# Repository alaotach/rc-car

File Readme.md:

# Quixie - RC Delivery Car

Quixie is a small autonomous RC delivery car. The custom PCB handles motor control and sensor expansion; the firmware manages navigation, telemetry, and the locking cargo bay.

> Built by **AlAoTach** for [Fallout](https://fallout.hackclub.com/)

---

## Why I Built This

I wanted to steal chips from my nephew.

---

## Key Features

- **Servo locked cargo bay** - lid opens and closes automatically via servo motor
- **Live camera feed** - ESP32-CAM streamed to the web dashboard
- **GPS navigation** - Neo-8M for real-time position tracking
- **Obstacle avoidance** - 3× ultrasonic sensors
- **OLED display** - SSD1306 1.3" on-device status screen
---

## Tech Specs

| Component | Part |
|-----------|------|
| MCU | ESP32 Mini (ESP32-S3) |
| Motors | Dual DC Geared, 12V |
| Driver | BTN7960B (43A) |
| GPS | Neo-6M |
| IMU | BMI270 |
| Sensors | Ultrasonic ×3 |
| Camera | ESP32-CAM |
| Display | SSD1306 OLED (1.11") |
| Battery | 3S Li-ion (11.1V) |
| Comms | WiFi — Web + WebSocket |

---

## System Overview

---

## What's in This Repo

```
quixie/
├── pcb/                          # KiCad project
│   ├── rc-car.kicad_pcb          # PCB layout
│   ├── rc-car.kicad_sch          # Schematic
│   ├── rc-car.kicad_pro          # Project file
│   ├── rc-car-BOM.csv            # Bill of materials
│   └── fabrication/              # Gerbers + drill files
├── firmware/
│   └── rc-car/
│       ├── include/              # Header files + Config.h
│       └── src/                  # Source files
├── fabrication/
│   └── 3d/
│       ├── rc-car-case.f3d       # Fusion 360 CAD source
│       ├── rc-car-case.stl       # 3D printable case
│       └── pcb-model.stl         # 3D PCB model
└── docs/assets/                  # Images and media
```

---

## PCB

Front and back of the custom PCB:

---

## 3D Case

The case is 3D printable in PLA.

**Open cargo bay**

---

## Schematic

### Main schema

### Motor schema

### Ultrasonic and TOF

### Servo lock

### Voltage divider

### Battery and charging

---

## Build Guide

### Step 1 - Export Gerbers

Open `pcb/rc-car.kicad_pcb` in KiCad. Generate Gerbers and drill files into `pcb/fabrication/`. Zip all outputs.

### Step 2 - Order the PCB

Upload your Gerber zip to [JLCPCB](https://jlcpcb.com) or your preferred fab.

### Step 3 - Solder & Populate

Solder the required components ( hope you have gotten SMD from jlcpcb )

### Step 4 - Flash Firmware

```bash
cd firmware/rc-car
pio run --target upload
```

Requires [PlatformIO](https://platformio.org/). Main config is in `firmware/rc-car/include/Config.h`.

### Step 5 - 3D Print the Case

- Material: PLA (PETG also works)
- File: `fabrication/3d/rc-car-case.stl`
- No supports needed for most orientations

### Step 6 - Final Assembly

Mount the PCB in the case, wire motors and power, connect sensors. The servo for the lid attaches at the rear hinge point.

---

## Modifying the Firmware

All config parameters live in:

```
firmware/rc-car/include/Config.h
```

Features are split into modules under `firmware/rc-car/src/`.

---

## License

Open source. Do what you want, just don't use it to steal chips from *my* nephew *cough cough*.

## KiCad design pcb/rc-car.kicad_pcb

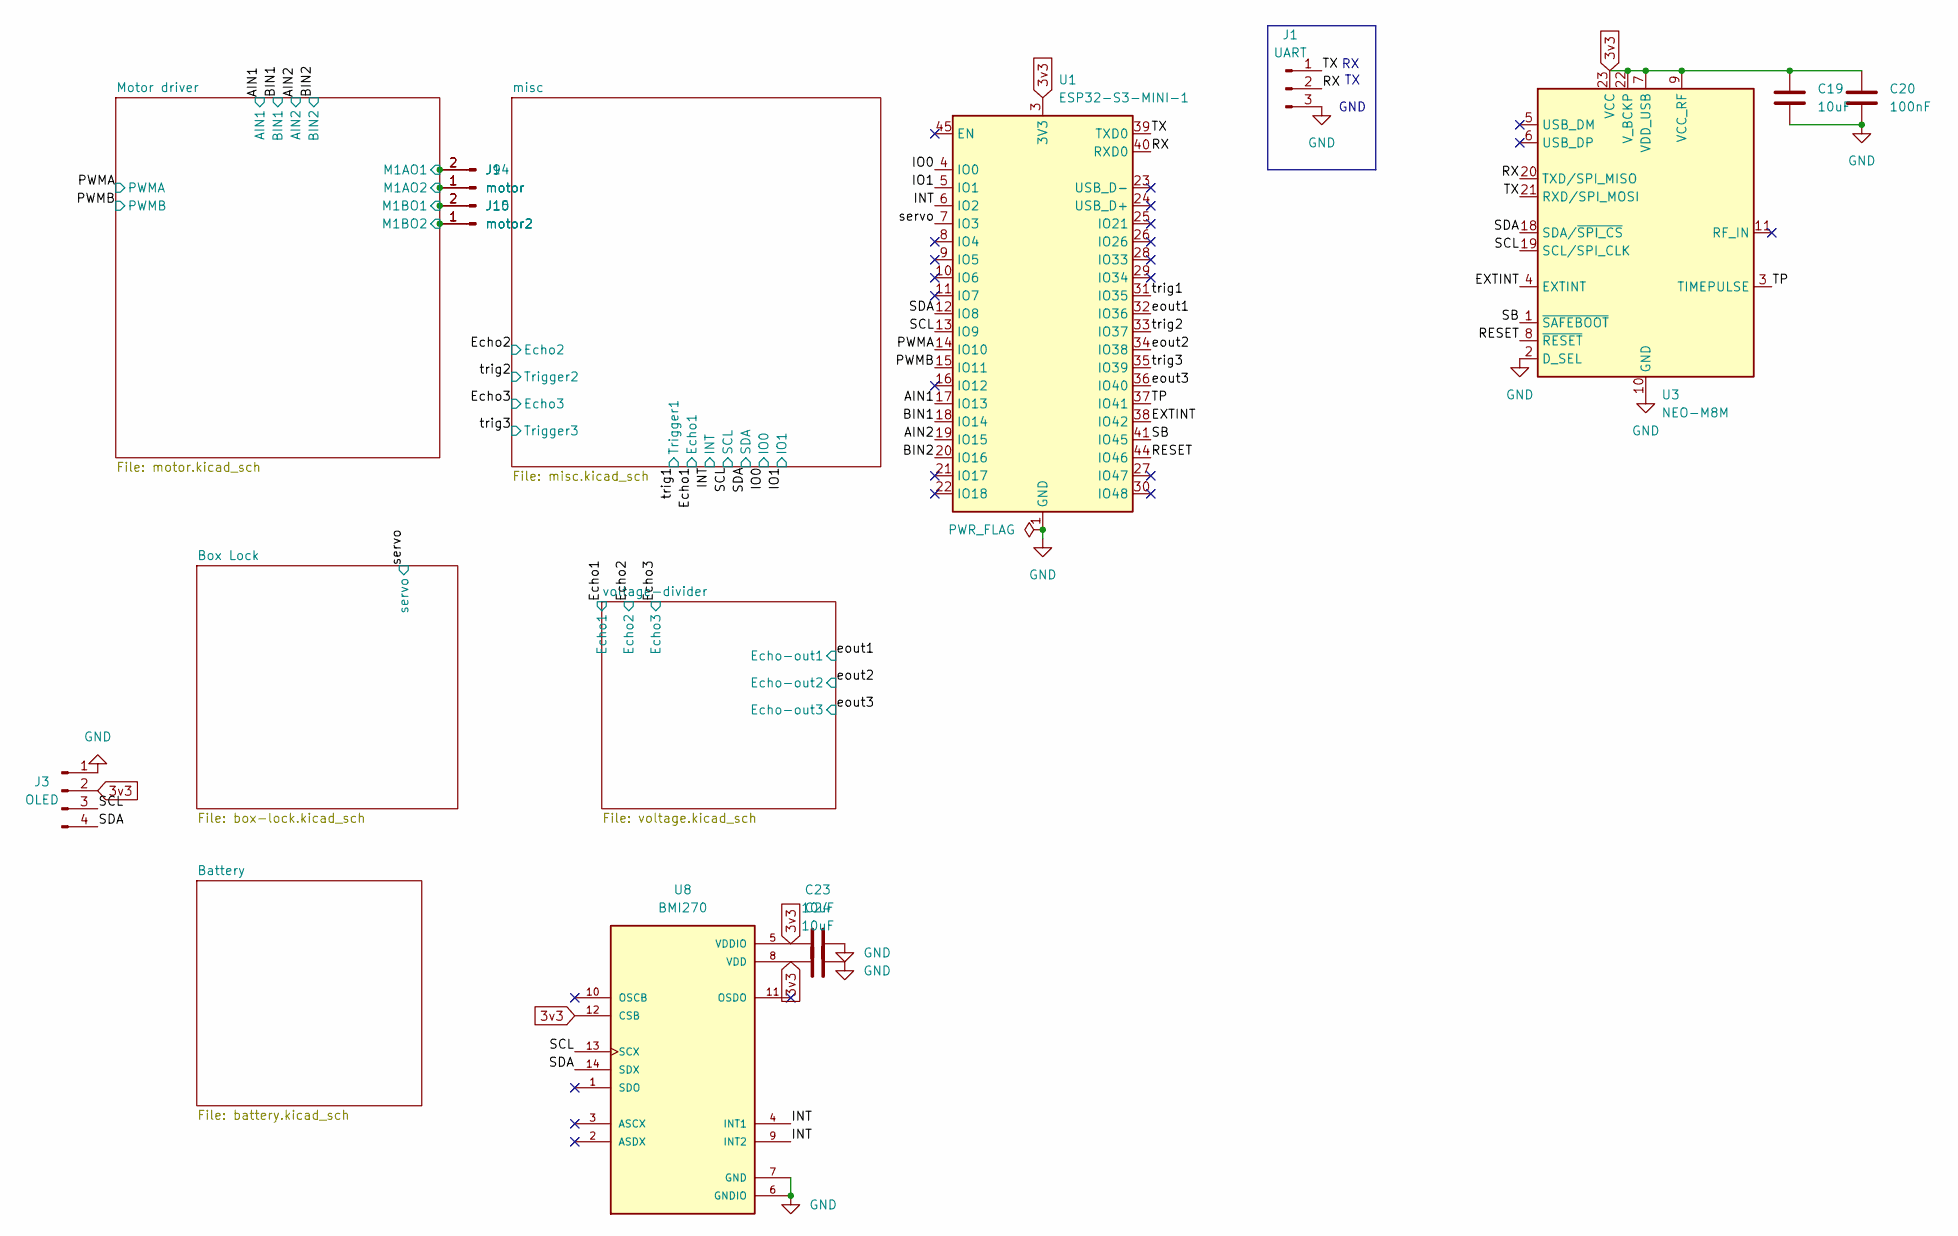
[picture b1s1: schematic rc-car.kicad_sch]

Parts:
C19, C23, C24: 10uF; C_0603_1608Metric
C20: 100nF; C_0603_1608Metric
J1: UART; PinHeader_1x03_P2.54mm_Vertical
J3: OLED; PinHeader_1x04_P2.54mm_Vertical
J9, J14: motor; PinHeader_1x02_P2.54mm_Vertical
J10, J15: motor2; PinHeader_1x02_P2.54mm_Vertical
U1: ESP32-S3-MINI-1; ESP32-S2-MINI-1
U3: NEO-M8M; ublox_NEO
U8: BMI270; XDCR_BMI270

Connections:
3v3: C19.1, C20.1, C23.1, C24.1, J3.2, U1.3 (3V3), U3.7 (VDD_USB), U3.9 (VCC_RF), U3.22 (V_BCKP), U3.23 (VCC), U8.5 (VDDIO), U8.8 (VDD), U8.12 (CSB); also elsewhere on the board
/AIN1: U1.17 (IO13); also elsewhere on the board
/AIN2: U1.19 (IO15); also elsewhere on the board
/BIN1: U1.18 (IO14); also elsewhere on the board
/BIN2: U1.20 (IO16); also elsewhere on the board
/EXTINT: U1.38 (IO42), U3.4 (EXTINT)
/INT: U1.6 (IO2), U8.4 (INT1), U8.9 (INT2); also elsewhere on the board
/IO0: U1.4 (IO0); also elsewhere on the board
/IO1: U1.5 (IO1); also elsewhere on the board
/Motor driver/M1AO1: J9.2, J14.2; also elsewhere on the board
/Motor driver/M1AO2: J9.1, J14.1; also elsewhere on the board
/Motor driver/M1BO1: J10.2, J15.2; also elsewhere on the board
/Motor driver/M1BO2: J10.1, J15.1; also elsewhere on the board
/PWMA: U1.14 (IO10); also elsewhere on the board
/PWMB: U1.15 (IO11); also elsewhere on the board
/RESET: U1.44 (IO46), U3.8 (~RESET)
/RX: J1.2, U1.40 (RXD0), U3.20 (TXD/SPI_MISO)
/SB: U1.41 (IO45), U3.1 (~SAFEBOOT)
/SCL: J3.3, U1.13 (IO9), U3.19 (SCL/SPI_CLK), U8.13 (SCX); also elsewhere on the board
/SDA: J3.4, U1.12 (IO8), U3.18 (SDA/~SPI_CS), U8.14 (SDX); also elsewhere on the board
/TP: U1.37 (IO41), U3.3 (TIMEPULSE)
/TX: J1.1, U1.39 (TXD0), U3.21 (RXD/SPI_MOSI)
/eout1: U1.32 (IO36); also elsewhere on the board
/eout2: U1.34 (IO38); also elsewhere on the board
/eout3: U1.36 (IO40); also elsewhere on the board
/servo: U1.7 (IO3); also elsewhere on the board
/trig1: U1.31 (IO35); also elsewhere on the board
/trig2: U1.33 (IO37); also elsewhere on the board
/trig3: U1.35 (IO39); also elsewhere on the board
GND: C19.2, C20.2, C23.2, C24.2, J1.3, J3.1, U1.1 (GND), U1.2 (GND), U1.42 (GND), U1.43 (GND), U1.46 (GND), U1.47 (GND), U1.48 (GND), U1.49 (GND), U1.50 (GND), U1.51 (GND), U1.52 (GND), U1.53 (GND), U1.54 (GND), U1.55 (GND), U1.56 (GND), U1.57 (GND), U1.58 (GND), U1.59 (GND), U1.60 (GND), U1.61 (GND), U1.62 (GND), U1.63 (GND), U1.64 (GND), U1.65 (GND), U3.2 (D_SEL), U3.10 (GND), U3.12 (GND), U3.13 (GND), U3.24 (GND), U8.6 (GNDIO), U8.7 (GND); also elsewhere on the board

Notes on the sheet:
GND

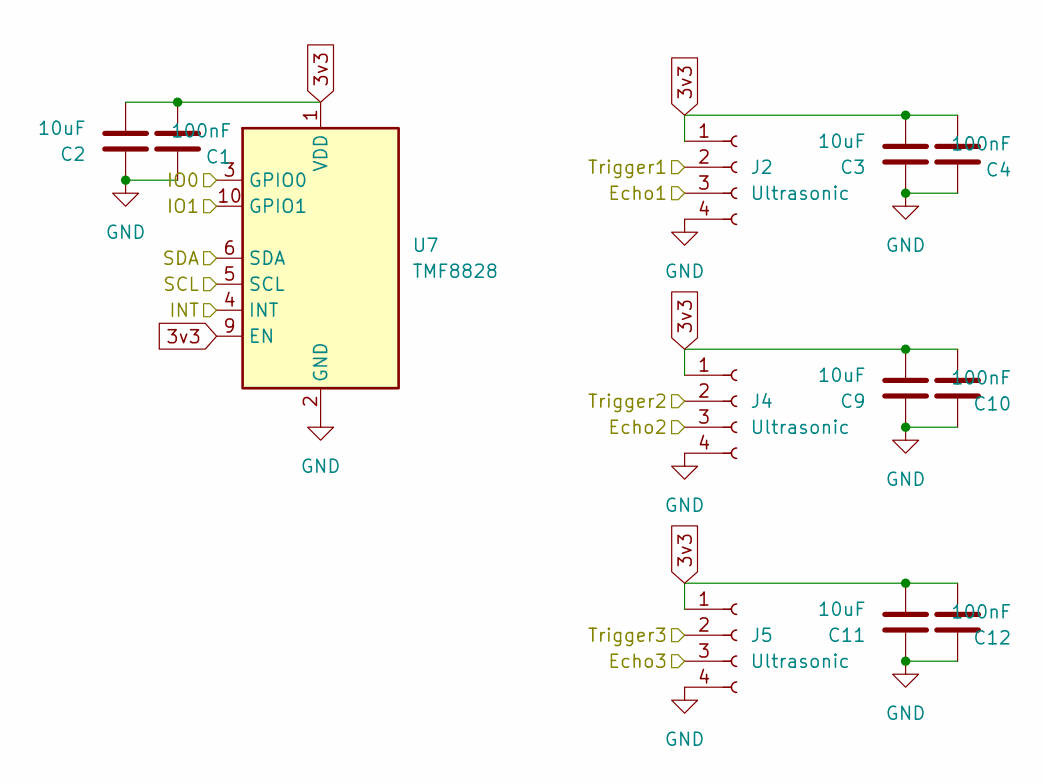
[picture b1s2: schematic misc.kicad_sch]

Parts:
C1, C4, C10, C12: 100nF; C_0603_1608Metric
C2, C3, C9, C11: 10uF; C_0603_1608Metric
J2, J4, J5: Ultrasonic; PinHeader_1x04_P2.54mm_Vertical
U7: TMF8828; AMS_OLGA12

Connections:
3v3: C1.1, C2.2, C3.2, C4.1, C9.2, C10.1, C11.2, C12.1, J2.1, J4.1, J5.1, U7.1 (VDD), U7.7 (VDD), U7.9 (EN), U7.12 (VDD); also elsewhere on the board
/Echo1: J2.3; also elsewhere on the board
/Echo2: J4.3; also elsewhere on the board
/Echo3: J5.3; also elsewhere on the board
/INT: U7.4 (INT); also elsewhere on the board
/IO0: U7.3 (GPIO0); also elsewhere on the board
/IO1: U7.10 (GPIO1); also elsewhere on the board
/SCL: U7.5 (SCL); also elsewhere on the board
/SDA: U7.6 (SDA); also elsewhere on the board
/trig1: J2.2; also elsewhere on the board
/trig2: J4.2; also elsewhere on the board
/trig3: J5.2; also elsewhere on the board
GND: C1.2, C2.1, C3.1, C4.2, C9.1, C10.2, C11.1, C12.2, J2.4, J4.4, J5.4, U7.2 (GND), U7.8 (GND), U7.11 (GND); also elsewhere on the board

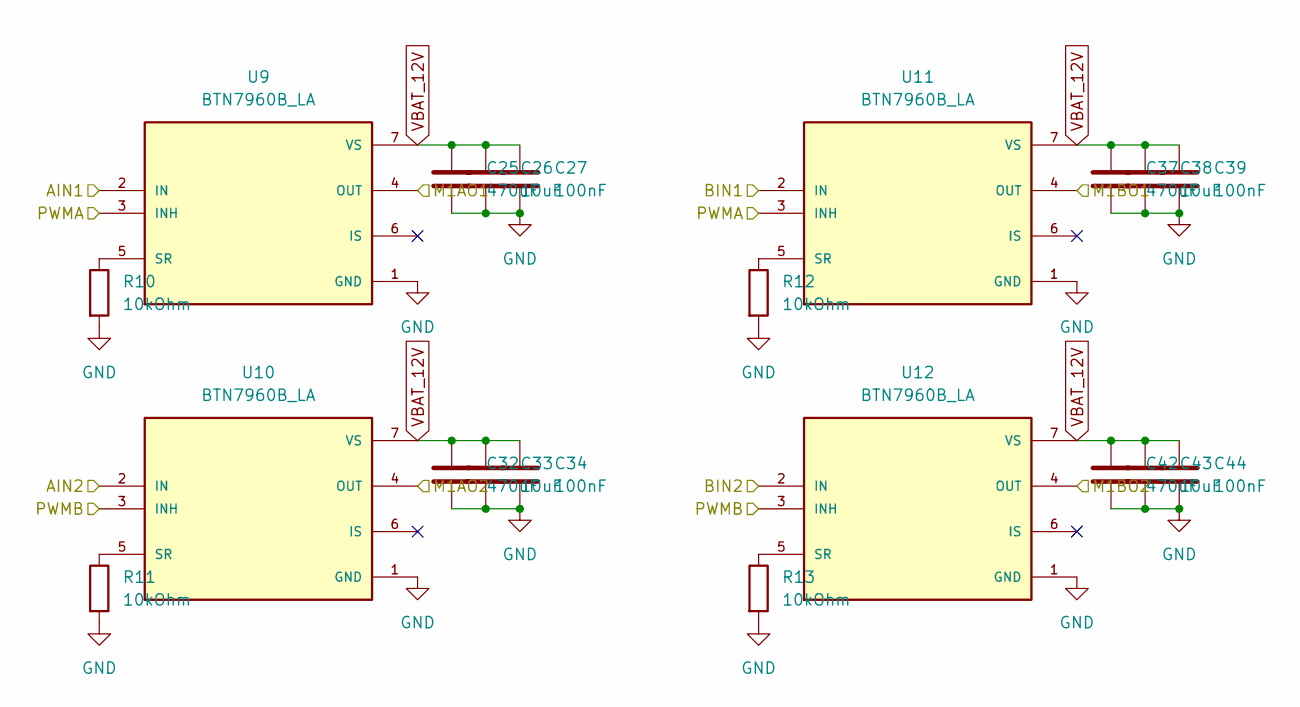
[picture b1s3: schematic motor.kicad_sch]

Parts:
C25, C32, C37, C42: 470uF; C_0603_1608Metric
C26, C33, C38, C43: 10uF; C_0603_1608Metric
C27, C34, C39, C44: 100nF; C_0603_1608Metric
R10, R11, R12, R13: 10kOhm; R_0603_1608Metric
U9, U10, U11, U12: BTN7960B_LA; IC_BTN7960B; PARTREV 1.0

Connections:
/AIN1: U9.2 (IN); also elsewhere on the board
/AIN2: U10.2 (IN); also elsewhere on the board
/BIN1: U11.2 (IN); also elsewhere on the board
/BIN2: U12.2 (IN); also elsewhere on the board
/Motor driver/M1AO1: U9.4 (OUT), U9.8 (OUT); also elsewhere on the board
/Motor driver/M1AO2: U10.4 (OUT), U10.8 (OUT); also elsewhere on the board
/Motor driver/M1BO1: U11.4 (OUT), U11.8 (OUT); also elsewhere on the board
/Motor driver/M1BO2: U12.4 (OUT), U12.8 (OUT); also elsewhere on the board
/PWMA: U9.3 (INH), U11.3 (INH); also elsewhere on the board
/PWMB: U10.3 (INH), U12.3 (INH); also elsewhere on the board
GND: C25.2, C26.2, C27.2, C32.2, C33.2, C34.2, C37.2, C38.2, C39.2, C42.2, C43.2, C44.2, R10.2, R11.2, R12.2, R13.2, U9.1 (GND), U10.1 (GND), U11.1 (GND), U12.1 (GND); also elsewhere on the board
unnamed: R10.1, U9.5 (SR)
unnamed: R11.1, U10.5 (SR)
unnamed: R12.1, U11.5 (SR)
unnamed: R13.1, U12.5 (SR)
VBAT_12V: C25.1, C26.1, C27.1, C32.1, C33.1, C34.1, C37.1, C38.1, C39.1, C42.1, C43.1, C44.1, U9.7 (VS), U10.7 (VS), U11.7 (VS), U12.7 (VS); also elsewhere on the board

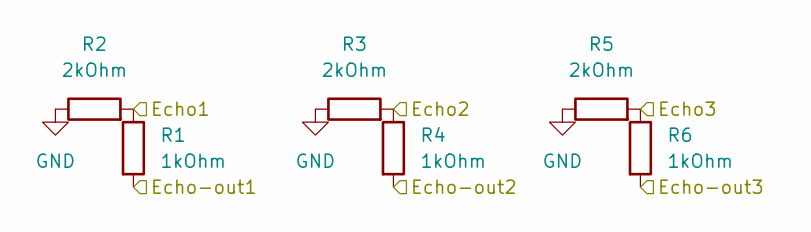
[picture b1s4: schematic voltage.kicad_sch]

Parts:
R1, R4, R6: 1kOhm; R_0603_1608Metric_Pad0.98x0.95mm_HandSolder
R2, R3, R5: 2kOhm; R_0603_1608Metric_Pad0.98x0.95mm_HandSolder

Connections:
/Echo1: R1.1, R2.2; also elsewhere on the board
/Echo2: R3.2, R4.1; also elsewhere on the board
/Echo3: R5.2, R6.1; also elsewhere on the board
/eout1: R1.2; also elsewhere on the board
/eout2: R4.2; also elsewhere on the board
/eout3: R6.2; also elsewhere on the board
GND: R2.1, R3.1, R5.1; also elsewhere on the board

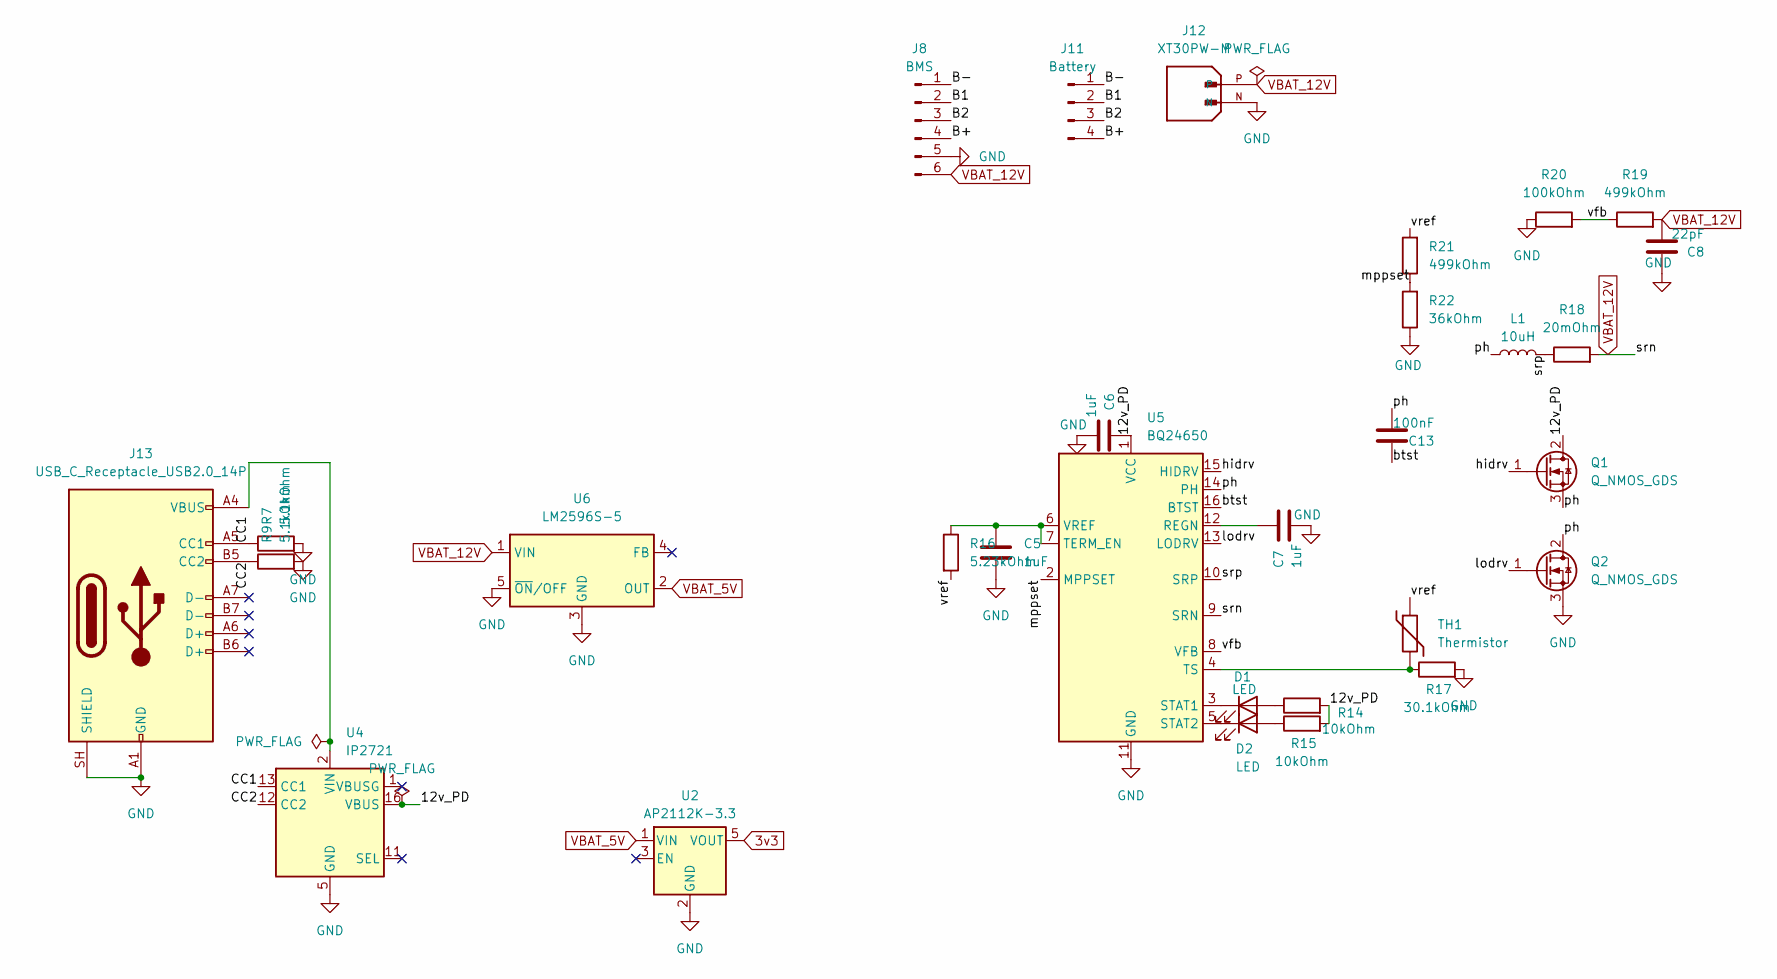
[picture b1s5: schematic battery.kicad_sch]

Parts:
C5, C6, C7: 1uF; C_0603_1608Metric
C8: 22pF; C_0603_1608Metric
C13: 100nF; C_0603_1608Metric
D1, D2: LED; LED_0201_0603Metric
J8: BMS; PinHeader_1x06_P2.54mm_Vertical
J11: Battery; JST_XH_B4B-XH-AM_1x04_P2.50mm_Vertical
J12: XT30PW-M; AMASS_XT30PW-M; PARTREV 1.2
J13: USB_C_Receptacle_USB2.0_14P; USB_C_Receptacle_HRO_TYPE-C-31-M-12
L1: 10uH; L_0201_0603Metric
Q1, Q2: Q_NMOS_GDS; TO-263-2
R7, R9: 5.1kOhm; R_0603_1608Metric_Pad0.98x0.95mm_HandSolder
R14, R15: 10kOhm; R_0603_1608Metric
R16: 5.23kOhm; R_0603_1608Metric
R17: 30.1kOhm; R_0603_1608Metric
R18: 20mOhm; R_0603_1608Metric
R19, R21: 499kOhm; R_0603_1608Metric
R20: 100kOhm; R_0603_1608Metric
R22: 36kOhm; R_0603_1608Metric
TH1: Thermistor; R_0805_2012Metric
U2: AP2112K-3.3; SOT-23-5
U4: IP2721; TSSOP-16_4.4x5mm_P0.65mm
U5: BQ24650; Texas_RVA_VQFN-16-1EP_3.5x3.5mm_P0.5mm_EP2.14x2.14mm_Therma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
U6: LM2596S-5; TO-263-5_TabPin3

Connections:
3v3: U2.5 (VOUT); also elsewhere on the board
/Battery/12v_PD: C6.1, Q1.2 (D), R14.2, R15.2, U4.16 (VBUS), U5.1 (VCC)
/Battery/B1: J8.2, J11.2
/Battery/B2: J8.3, J11.3
/Battery/B+: J8.4, J11.4
/Battery/B-: J8.1, J11.1
/Battery/CC1: J13.A5 (CC1), R7.1, U4.13 (CC1)
/Battery/CC2: J13.B5 (CC2), R9.1, U4.12 (CC2)
/Battery/btst: C13.1, U5.16 (BTST)
/Battery/hidrv: Q1.1 (G), U5.15 (HIDRV)
/Battery/lodrv: Q2.1 (G), U5.13 (LODRV)
/Battery/mppset: R21.1, R22.2, U5.2 (MPPSET)
/Battery/ph: C13.2, L1.1, Q1.3 (S), Q2.2 (D), U5.14 (PH)
/Battery/srp: L1.2, R18.1, U5.10 (SRP)
/Battery/vfb: R19.1, R20.2, U5.8 (VFB)
/Battery/vref: R16.2, R21.2, TH1.1
GND: C5.2, C6.2, C7.2, C8.1, J8.5, J12.N, J13.A1 (GND), J13.A12 (GND), J13.B1 (GND), J13.B12 (GND), J13.SH (SHIELD), Q2.3 (S), R7.2, R9.2, R17.2, R20.1, R22.1, U2.2 (GND), U4.5 (GND), U5.11 (GND), U5.17 (GND), U6.3 (GND), U6.5 (~ON/OFF); also elsewhere on the board
unnamed: D1.2 (A), R14.1
unnamed: D1.1 (K), U5.3 (STAT1)
unnamed: D2.2 (A), R15.1
unnamed: D2.1 (K), U5.5 (STAT2)
unnamed: J13.A4 (VBUS), J13.A9 (VBUS), J13.B4 (VBUS), J13.B9 (VBUS), U4.2 (VIN)
unnamed: C7.1, U5.12 (REGN)
unnamed: C5.1, R16.1, U5.6 (VREF), U5.7 (TERM_EN)
unnamed: R17.1, TH1.2, U5.4 (TS)
VBAT_5V: U2.1 (VIN), U6.2 (OUT); also elsewhere on the board
VBAT_12V: C8.2, J8.6, J12.P, R18.2, R19.2, U5.9 (SRN), U6.1 (VIN); also elsewhere on the board

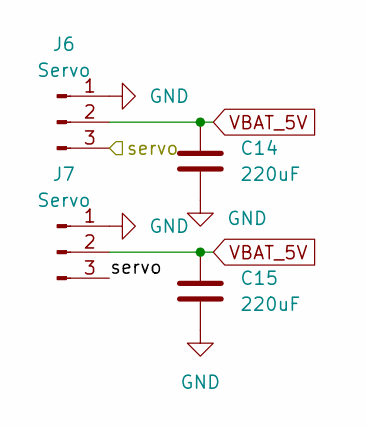
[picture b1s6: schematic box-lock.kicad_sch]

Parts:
C14, C15: 220uF; C_0603_1608Metric
J6, J7: Servo; PinHeader_1x03_P2.54mm_Vertical

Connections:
/servo: J6.3, J7.3; also elsewhere on the board
GND: C14.2, C15.1, J6.1, J7.1; also elsewhere on the board
VBAT_5V: C14.1, C15.2, J6.2, J7.2; also elsewhere on the board

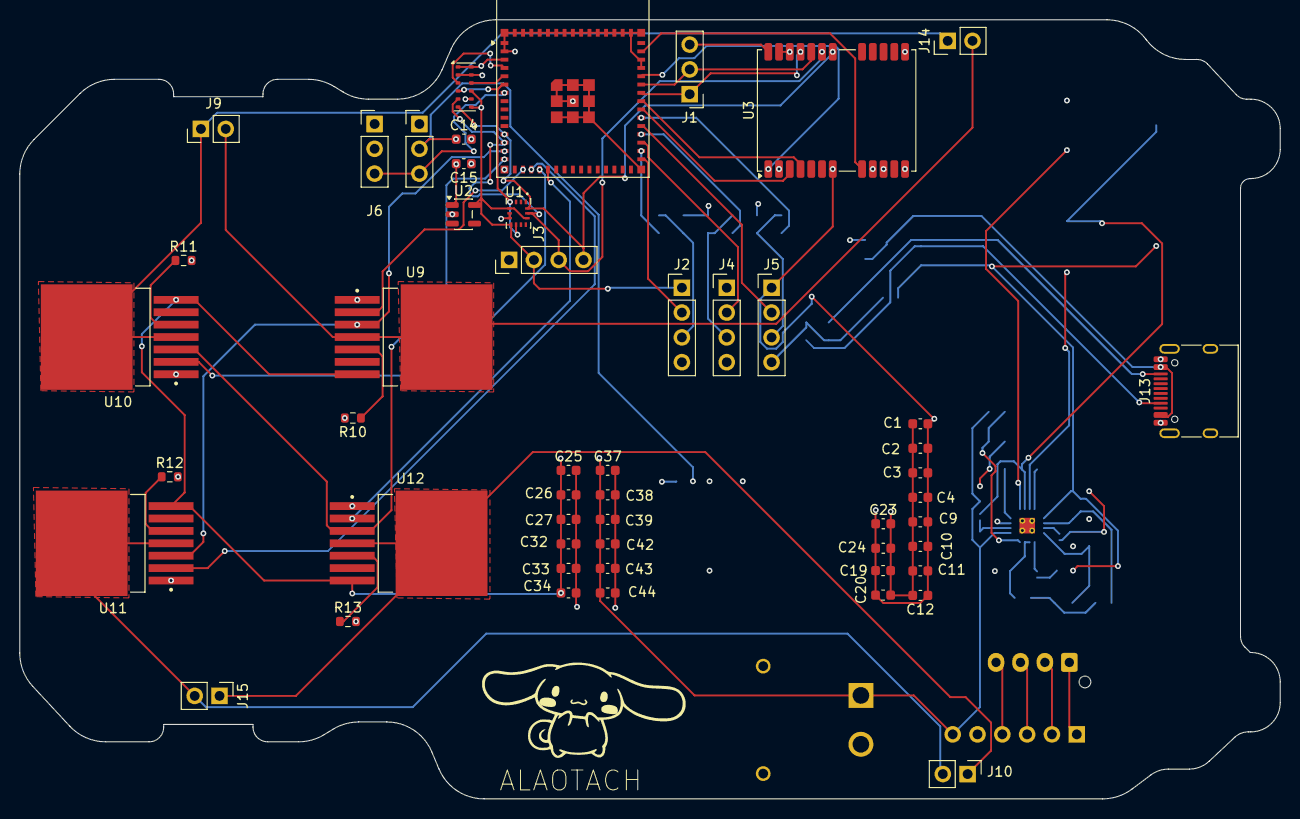
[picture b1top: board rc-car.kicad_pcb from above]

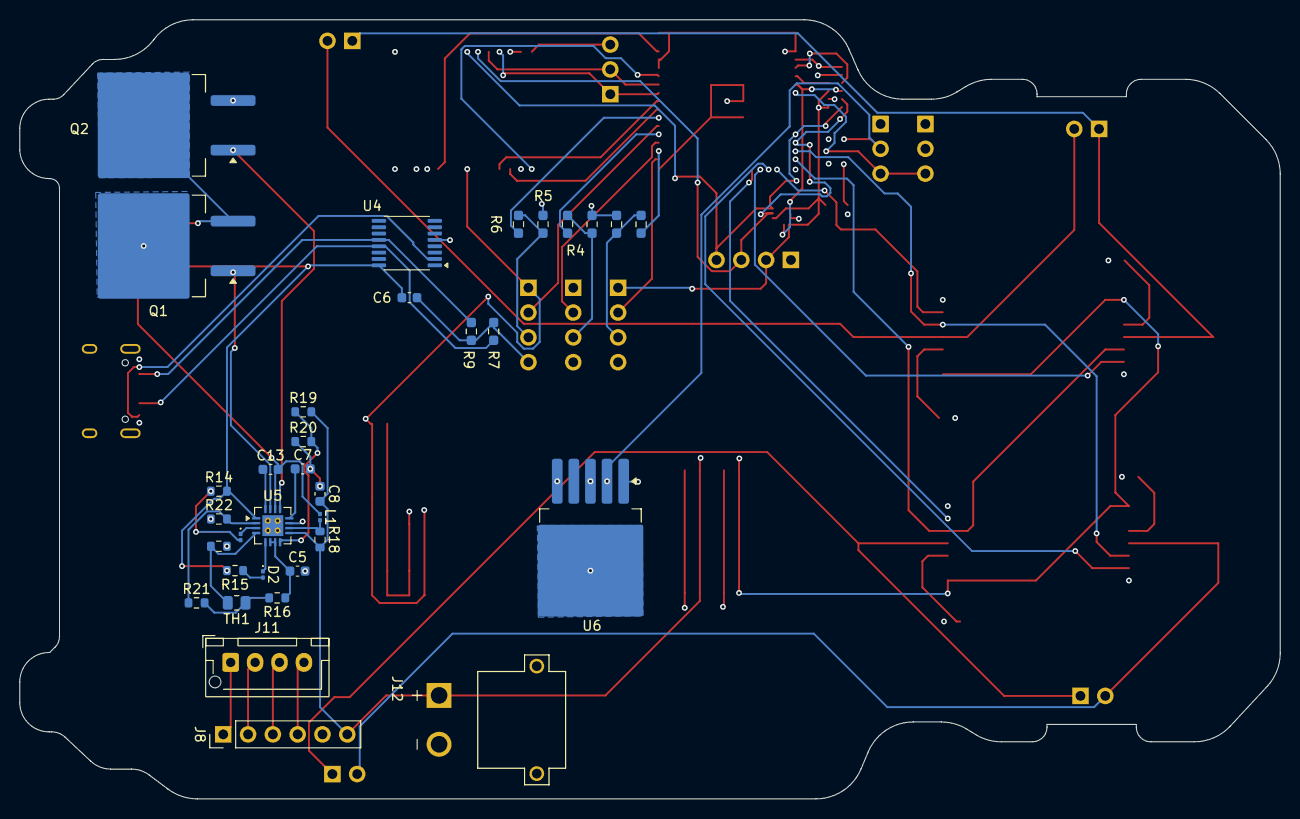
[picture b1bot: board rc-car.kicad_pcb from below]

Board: 4 copper layers, 129.0 x 79.8 mm, 85 parts (34 on the bottom side), 62 nets.

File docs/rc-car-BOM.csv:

Reference,Qty,Value,Footprint,Price,Total Price,URL
"C1,C4,C10,C12,C13,C20,C27,C34,C39,C44",10,100nF,Capacitor_SMD:C_0603_1608Metric,0.07,0.7,
"C2,C3,C9,C11,C19,C23,C24,C26,C33,C38,C43",11,10uF,Capacitor_SMD:C_0603_1608Metric,0.07,0.77,
"C5,C6,C7",3,1uF,Capacitor_SMD:C_0603_1608Metric,0.07,0.21,
C8,1,22pF,Capacitor_SMD:C_0603_1608Metric,0.07,0.07,
"C14,C15",2,220uF,Capacitor_SMD:C_0603_1608Metric,0.07,0.14,
"C25,C32,C37,C42",4,470uF,Capacitor_SMD:C_0603_1608Metric,0.07,0.28,
"D1,D2",2,LED,LED_SMD:LED_0201_0603Metric,0.07,0.14,
J1,1,UART,Connector_PinHeader_2.54mm:PinHeader_1x03_P2.54mm_Vertical,3.1,3.1,https://www.electropi.in/usb-to-serial-adapter-module-usb-to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
"J2,J4,J5",3,Ultrasonic,Connector_PinHeader_2.54mm:PinHeader_1x04_P2.54mm_Vertical,0.72,2.16,https://robu.in/product/hc-sr04-ultrasonic-range-finder/
J3,1,OLED,Connector_PinHeader_2.54mm:PinHeader_1x04_P2.54mm_Vertical,4.05,4.05,https://robu.in/product/1-3-oled-display-v2/
"J6,J7",2,Servo,Connector_PinHeader_2.54mm:PinHeader_1x03_P2.54mm_Vertical,2.4,4.8,https://www.amazon.in/DHRUVPRO-Micro-Servo-Motor-Helicopter/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
J8,1,BMS,Connector_PinHeader_2.54mm:PinHeader_1x06_P2.54mm_Vertical,3.7,3.7,https://www.amazon.in/LAND-INDIA-40A-BMS-Over-Discharge/dp/B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
"J9,J14, J10,J15",4,motor,Connector_PinHeader_2.54mm:PinHeader_1x02_P2.54mm_Vertical,2.68,10.72,https://robu.in/product/200rpm-12v-low-noise-dc-motor-with-m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
,,,,,0,
J11,1,Battery,Connector_JST:JST_XH_B4B-XH-AM_1x04_P2.50mm_Vertical,12.9,12.9,https://www.electropi.in/11.1v-2200mah-lipo-battery-india
J12,1,XT30PW-M,XT30PW-M:AMASS_XT30PW-M,0.5,0.5,https://robu.in/product/amass-xt30pw30-female-connector-xt30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
J13,1,USB_C_Receptacle_USB2.0_14P,Connector_USB:USB_C_Receptacle_HRO_TYPE-C-31-M-12,,1,
L1,1,10uH,Inductor_SMD:L_0201_0603Metric,0.07,0.07,
"Q1,Q2",2,Q_NMOS_GDS,Package_TO_SOT_SMD:TO-263-2,0.5,1,
"R1,R4,R6",3,1kOhm,Resistor_SMD:R_0603_1608Metric_Pad0.98x0.95mm_HandSolder,0.07,0.21,
"R2,R3,R5",3,2kOhm,Resistor_SMD:R_0603_1608Metric_Pad0.98x0.95mm_HandSolder,0.07,0.21,
"R7,R9",2,5.1kOhm,Resistor_SMD:R_0603_1608Metric_Pad0.98x0.95mm_HandSolder,0.07,0.14,
"R10,R11,R12,R13,R14,R15",6,10kOhm,Resistor_SMD:R_0603_1608Metric,0.07,0.42,
R16,1,5.23kOhm,Resistor_SMD:R_0603_1608Metric,0.07,0.07,
R17,1,30.1kOhm,Resistor_SMD:R_0603_1608Metric,0.07,0.07,
R18,1,20mOhm,Resistor_SMD:R_0603_1608Metric,0.07,0.07,
"R19,R21",2,499kOhm,Resistor_SMD:R_0603_1608Metric,0.07,0.14,
R20,1,100kOhm,Resistor_SMD:R_0603_1608Metric,0.07,0.07,
R22,1,36kOhm,Resistor_SMD:R_0603_1608Metric,0.07,0.07,
TH1,1,Thermistor,Resistor_SMD:R_0805_2012Metric,0.07,0.07,
U1,1,ESP32-S3-MINI-1,RF_Module:ESP32-S2-MINI-1,18.7,18.7,https://www.amazon.in/dp/B0G8ZWDDM6
U2,1,AP2112K-3.3,Package_TO_SOT_SMD:SOT-23-5,0.25,0.25,https://robu.in/product/ap2112k-1-8trg1-diodes-incorporated-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
U3,1,NEO-M8M,RF_GPS:ublox_NEO,10.2,10.2,https://robu.in/product/apm2-5-ublox-neo-m8n-gps-module-gygp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
U4,1,IP2721,Package_SO:TSSOP-16_4.4x5mm_P0.65mm,1,1,https://www.jakelectronics.com/productdetail/injoinic-ip2721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
U5,1,BQ24650,Package_DFN_QFN:Texas_RVA_VQFN-16-1EP_3.5x3.5mm_P0.5mm_EP2.14x2.14mm_ThermalVias,6,6,https://www.lioncircuits.com/parts/BQ24650RVAR?srsltid=AfmBO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
U6,1,LM2596S-5,Package_TO_SOT_SMD:TO-263-5_TabPin3,0.7,0.7,https://robu.in/product/lm2596s-5-0-xblw-step-down-type-fixe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
U7,1,TMF8828,Sensor_Distance:AMS_OLGA12,1.32,1.32,https://robu.in/product/vl53l0x-tof-based-lidar-laser-distan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
U8,1,BMI270,BMI270:XDCR_BMI270,3.4,3.4,https://www.utmel.com/productdetail/boschsensortec-bmi270-61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
"U9,U10,U11,U12",4,BTN7960B_LA,BTN7960B:IC_BTN7960B,1.55,6.2,https://www.ktron.in/product/bts7960-motor-driver-ic-43a-h-b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
,,,,,95.62,

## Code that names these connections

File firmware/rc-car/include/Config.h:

#ifndef CONFIG_H
#define CONFIG_H

#define WIFI_SSID "Samsung a35"
#define WIFI_PASS "samsung1"
#define GPS_RX 19
#define GPS_TX 20
#define MOTORPWMA 10
#define MOTORPWMB 11
#define MOTORAIN1 13
#define MOTORAIN2 15
#define MOTORBIN1 14
#define MOTORBIN2 16
#define TRIG1 35
#define TRIG2 37
#define TRIG3 39
#define ECHO1 36
#define ECHO2 38
#define ECHO3 40
#define SERVO 3

#endif

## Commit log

2026-05-30 created required header files
2026-05-30 gps, motor and ultrasonic sensor basic done
2026-05-30 basic navigation system, obstacle avoidance, go to waypoint etc
2026-05-30 wifi connection and webserver with websockets for commands
2026-05-30 basic firmware done
2026-05-31 files organized and readme
2026-05-31 Add additional details to Readme.md
2026-06-10 case update
2026-06-10 case
